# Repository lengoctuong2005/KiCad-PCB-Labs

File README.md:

# HCMUT - Thiết Kế Mạch In PCB với KiCad (Khóa Hè)

Tập hợp toàn bộ các bài thực hành và đồ án thiết kế PCB (KiCad) trong khóa học Thiết kế Mạch In / Vi Mạch.

## 📂 Danh mục bài tập (Labs & Project)

- **Common_Libraries/**: Thư viện linh kiện Footprint và Symbol tự tạo dùng chung.
- **Lab1/**: Thiết kế Mạch Nguồn Cơ Bản (Schematic, PCB Layout, Báo cáo kỹ thuật).
- **Lab2/**: Mạch Khuếch Đại / Cảm Biến & Sắp xếp linh kiện tiêu chuẩn.
- **Lab3/**: Mạch Giao Tiếp & Chuyển Đổi Nguồn (Schematic, Routing 2 lớp, BOM, Báo cáo & Kiểm tra DRC/ERC).
- **Lab4/**: Mạch Vi Điều Khiển / Ngoại Vi Mở Rộng.
- **Lab5/**: Thiết Kế Mạch RF / Cao Tần & Layout Nâng Cao.
- **Lab6/**: Tổng Hợp Thiết Kế Hoàn Chỉnh & Xuất File Gia Công (Gerber, Drill, BOM, CPL).
- **DoAn/**: Tài liệu và danh mục đề tài Đồ Án Cuối Khóa.

## 🛠️ Công cụ sử dụng
- **KiCad EDA v8 / v9**
- Schematic Editor (`.kicad_sch`)
- PCB Editor (`.kicad_pcb`)
- Footprint & Symbol Libraries (`.kicad_mod`, `.kicad_sym`)

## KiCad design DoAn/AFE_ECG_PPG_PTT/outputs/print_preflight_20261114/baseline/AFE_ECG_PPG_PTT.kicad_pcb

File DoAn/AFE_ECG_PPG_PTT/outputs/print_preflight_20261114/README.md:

# Gói kiểm trước đặt PCB trần và bộ tài liệu bench, cập nhật 18/11/2026

## Phạm vi bàn giao

PCB prototype 92 x 70 mm, hai lớp, dùng cho thử nghiệm bench với tín hiệu giả lập. Bản cập nhật ngày 18/11/2026 bổ sung đầy đủ thuộc tính `MPN` và `LCSC` đồng nhất trên toàn bộ 46 ký hiệu schematic và 46 footprint PCB, tạo `BOM_Orderable_LCSC.csv` đặt hàng LCSC, dựng bộ ảnh kiểm tra CAM từ dữ liệu Gerber và Excellon thực tế trong ZIP, và tạo bản đồ hàn lắp tương tác `Interactive_Soldering_Guide.html`. Không thay đổi `firmware/esp32_ptt_streamer/main.c` và `main/main.c`. Không chứng minh mạch hoạt động hoặc an toàn dùng trên người.

**File gửi CAM:** `GERBER_ONLY_92x70_NOT_CAM_APPROVED.zip`. Có đúng 11 file cấp gốc: 9 Gerber và 2 Excellon, không PDF/README/BOM/build. `.gbrjob` nằm ngoài ZIP.

## Kiểm đã làm ngày 18/11/2026

- KiCad 10.0.8 DRC với `--refill-zones --all-track-errors --schematic-parity --severity-all --exit-code-violations`: 0 violation, 0 unconnected, 0 schematic parity kể cả `footprint_symbol_field_mismatch`, `ignored_checks` rỗng.
- ERC đạt 0 Errors và 0 Warnings; giữ hai kiểm không áp dụng `global label only appears once` và `SPICE model issue` trong `erc.rpt`.
- Kiểm profile tạm `min_silk_clearance` 0,15 mm, `silk_over_copper` = error, `silk_overlap` = error, `silk_edge_clearance` = error đạt 0 lỗi trong `drc_fab_silk15.json`.
- Bảy kiểm regression `tests/check_*.py` đều PASS và 10/10 cổng `tools/bench_bringup_verify.py --preflight` đều PASS.
- 90 lỗ/slot khớp PCB trong 0,0011 mm: 38 via drill 0,3 mm; 48 lỗ/slot tool 1 mm gồm 3 slot `G85` tại `J1`; 4 lỗ M3 3,2 mm có mạ. NPTH file rỗng là chủ ý.
- Dựng kiểm tra CAM trực tiếp từ các tệp giải nén trong ZIP bằng Pillow/Excellon parser tại `CAM_top.png`, `CAM_bottom.png`, `CAM_mask.png`, `CAM_paste.png` và lưu thông số vào `gerbv_logs.json`: xác nhận 3 slot `G85` ở `J1`, 38/38 via phủ mask kín trên cả `F.Mask` và `B.Mask`, và 4 cửa sổ stencil phân đoạn `1,05 x 1,05 mm` đạt 65,2% diện tích trên EP của `U1`. Môi trường chạy không cài `gerbv`, nên cần đối chiếu thêm bằng preview CAM của xưởng trước khi thanh toán.
- `BOM.csv` xuất đủ 6 cột `Reference,Value,Footprint,MPN,LCSC,Quantity` cho 46 hàng; `BOM_Orderable_LCSC.csv` gồm 20 dòng linh kiện đặt hàng với `J2` số lượng 2 thanh.
- `Interactive_Soldering_Guide.html` tạo từ tọa độ thực trong `.kicad_pcb` cùng bảng MPN/LCSC và điểm kiểm tra `TP1..TP7`.
- `manifest.json` lưu mã băm SHA-256 của toàn bộ tệp nguồn, test và gói xuất hiện hành.

## Cách đặt và hàn lắp

Đọc `../HUONG_DAN_IN_HAN_VA_NGHIEM_THU.md`, `DAT_PCB_TRAN.md` và `FAB_PROFILE.md`. In `Assembly_1to1.pdf` tỷ lệ 100% đối chiếu module thực và mở `Interactive_Soldering_Guide.html` khi hàn lắp.

## Các cổng chưa đóng

1. Trước thanh toán: xác nhận preview CAM của xưởng nhận đúng 92 x 70 mm, 2 lớp, 3 slot `G85` của `J1`, 38 via tented và 4 lỗ M3 mạ; kiểm tồn kho thực tế của `U2` `C37593`, `C6/C7` `C82282`, `R16/R17` `C23162`, `R18` `C38070` và khớp cơ khí `J1` `SJ1-3533N`.
2. Trước lắp và cấp nguồn: kiểm tra pinout 7 chân và pull-up của module `MAX30102` thực mua ngoài, kiểm tra khớp chân ESP32 DevKitC V4 38 chân với `J2`.
3. Sau lắp: chạy `tools/esp32_bench_diag/esp32_bench_diag.ino` kiểm tra I2C và ngưỡng LOD `1400 mV` trên `GPIO32`/`GPIO33`, thực hiện đo 7 bước bench với máy giả lập và giữ nguyên khóa PAT live do `TIMESTAMP_UNCERTAIN`.

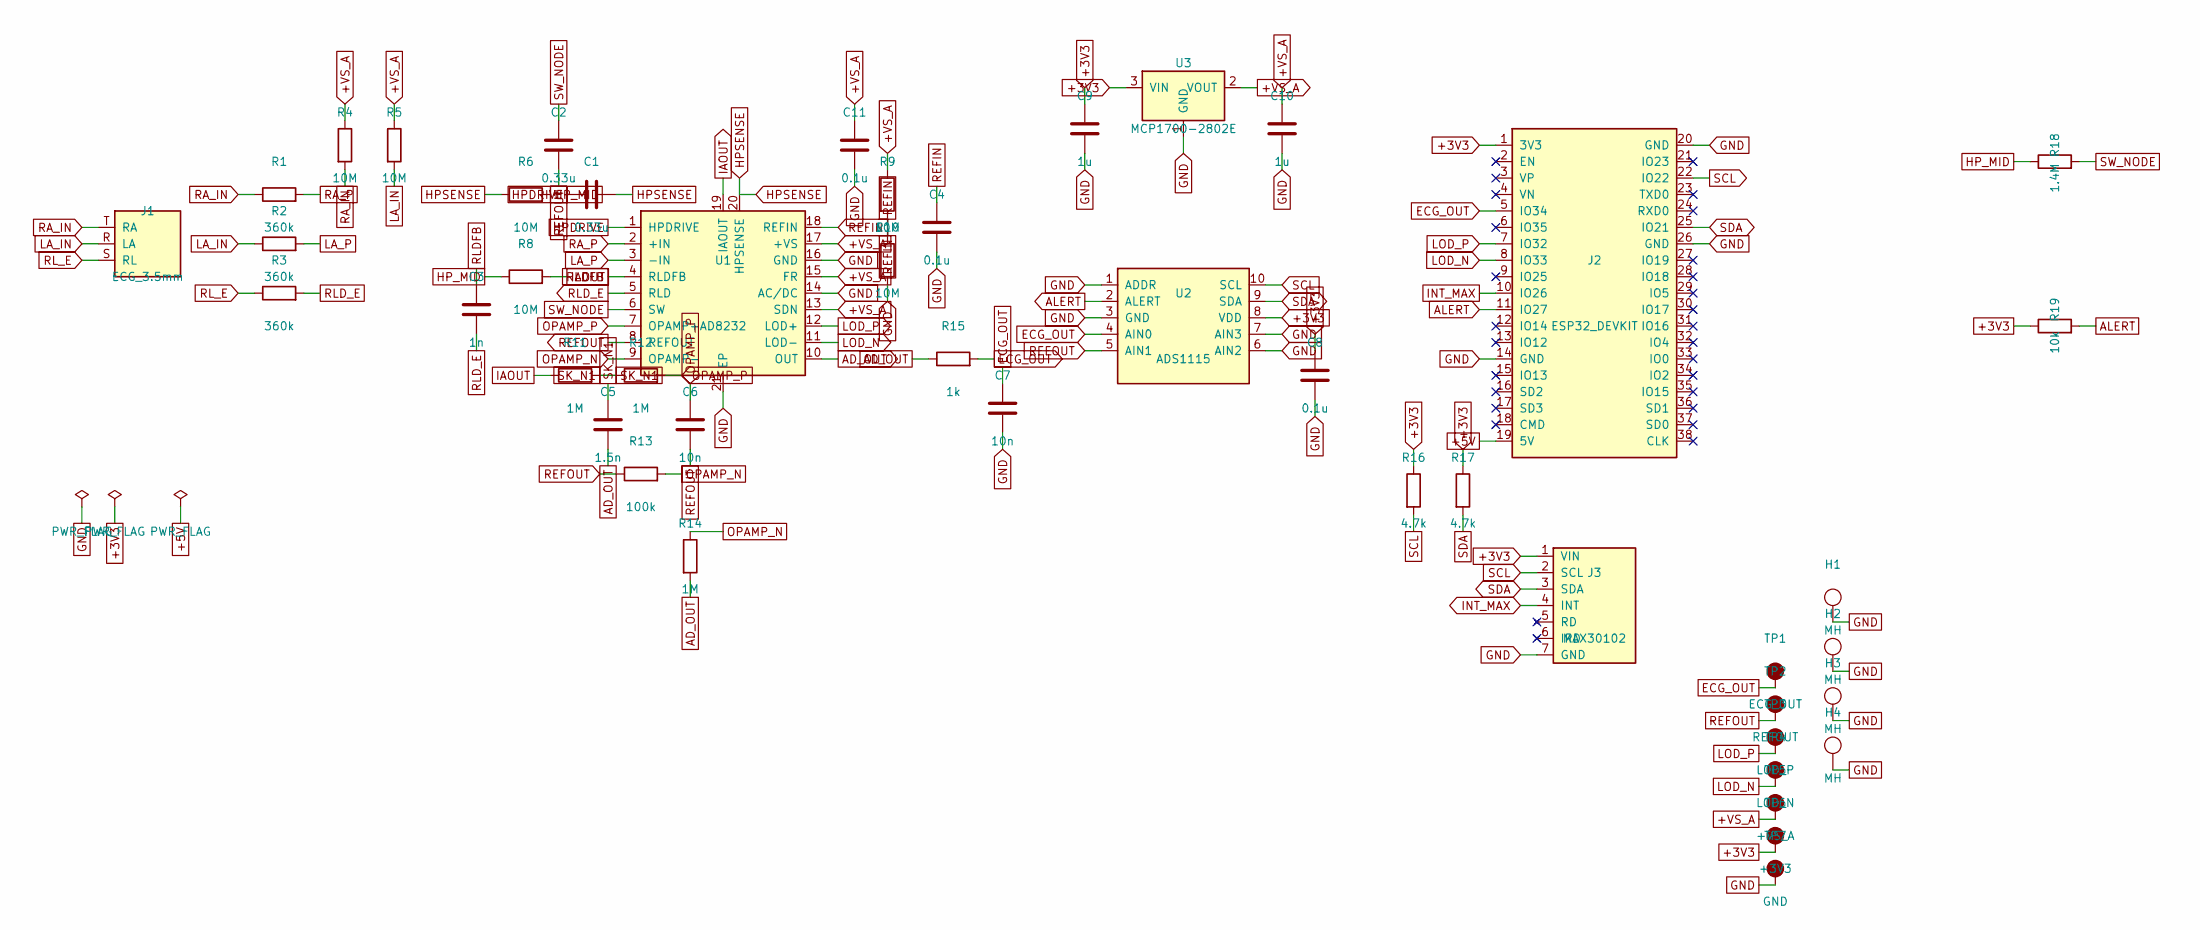
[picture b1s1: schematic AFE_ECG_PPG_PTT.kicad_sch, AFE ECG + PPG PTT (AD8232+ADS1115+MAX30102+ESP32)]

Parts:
C1, C2: 0.33u; C_0603_1608Metric
C3: 1n; C_0603_1608Metric
C4, C8, C11: 0.1u; C_0603_1608Metric
C5: 1.5n; C_0603_1608Metric
C6, C7: 10n; C_0603_1608Metric
C9, C10: 1u; C_0603_1608Metric
H1, H2, H3, H4: MH; MountingHole_3.2mm_M3_Pad
J1: ECG_3.5mm; Jack_3.5mm_CUI_SJ1-3533NG_Horizontal
J2: ESP32_DEVKIT; ESP32_DevKitC_V4_38P
J3: MAX30102; PinHeader_1x07_P2.54mm_Vertical
R1, R2, R3: 360k; R_0603_1608Metric
R4, R5, R6, R8, R9, R10: 10M; R_0603_1608Metric
R11, R12, R14: 1M; R_0603_1608Metric
R13: 100k; R_0603_1608Metric
R15: 1k; R_0603_1608Metric
R16, R17: 4.7k; R_0603_1608Metric
R18: 1.4M; R_0603_1608Metric
R19: 10k; R_0603_1608Metric
TP1: ECG_OUT; TestPoint_Pad_D1.5mm
TP2: REFOUT; TestPoint_Pad_D1.5mm
TP3: LOD_P; TestPoint_Pad_D1.5mm
TP4: LOD_N; TestPoint_Pad_D1.5mm
TP5: +VS_A; TestPoint_Pad_D1.5mm
TP6: +3V3; TestPoint_Pad_D1.5mm
TP7: GND; TestPoint_Pad_D1.5mm
U1: AD8232; LFCSP-20-1EP_4x4mm_P0.5mm_EP2.6x2.6mm
U2: ADS1115; TSSOP-10_3x3mm_P0.5mm
U3: MCP1700-2802E; SOT-23

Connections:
+3V3: C8.1, C9.1, J2.1 (3V3), J3.1 (VIN), R16.1, R17.1, R19.1, TP6.1, U2.8 (VDD), U3.3 (VIN)
+5V: J2.19 (5V)
+VS_A: C10.1, C11.1, R4.1, R5.1, R9.1, TP5.1, U1.13 (SDN), U1.15 (FR), U1.17 (+VS), U3.2 (VOUT)
AD_OUT: C5.2, R14.2, R15.1, U1.10 (OUT)
ALERT: J2.11 (IO27), R19.2, U2.2 (ALERT)
ECG_OUT: C7.1, J2.5 (IO34), R15.2, TP1.1, U2.4 (AIN0)
GND: C4.2, C7.2, C8.2, C9.2, C10.2, C11.2, H1.1, H2.1, H3.1, H4.1, J2.14 (GND), J2.20 (GND), J2.26 (GND), J3.7 (GND), R10.2, TP7.1, U1.14 (AC/DC), U1.16 (GND), U1.21 (EP), U2.1 (ADDR), U2.3 (GND), U2.6 (AIN2), U2.7 (AIN3), U3.1 (GND)
HPDRIVE: C1.1, U1.1 (HPDRIVE)
HPSENSE: C1.2, R6.1, U1.20 (HPSENSE)
HP_MID: R6.2, R8.1, R18.1
IAOUT: R8.2, R11.1, U1.19 (IAOUT)
INT_MAX: J2.10 (IO26), J3.4 (INT)
LA_IN: J1.R (LA), R2.1, R5.2
LA_P: R2.2, U1.3 (-IN)
LOD_N: J2.8 (IO33), TP4.1, U1.11 (LOD-)
LOD_P: J2.7 (IO32), TP3.1, U1.12 (LOD+)
OPAMP_N: R13.2, R14.1, U1.9 (OPAMP-)
OPAMP_P: C6.1, R12.2, U1.7 (OPAMP+)
RA_IN: J1.T (RA), R1.1, R4.2
RA_P: R1.2, U1.2 (+IN)
REFIN: C4.1, R9.2, R10.1, U1.18 (REFIN)
REFOUT: C2.2, C6.2, R13.1, TP2.1, U1.8 (REFOUT), U2.5 (AIN1)
RLDFB: C3.1, U1.4 (RLDFB)
RLD_E: C3.2, R3.2, U1.5 (RLD)
RL_E: J1.S (RL), R3.1
SCL: J2.22 (IO22), J3.2 (SCL), R16.2, U2.10 (SCL)
SDA: J2.25 (IO21), J3.3 (SDA), R17.2, U2.9 (SDA)
SK_N1: C5.1, R11.2, R12.1
SW_NODE: C2.1, R18.2, U1.6 (SW)

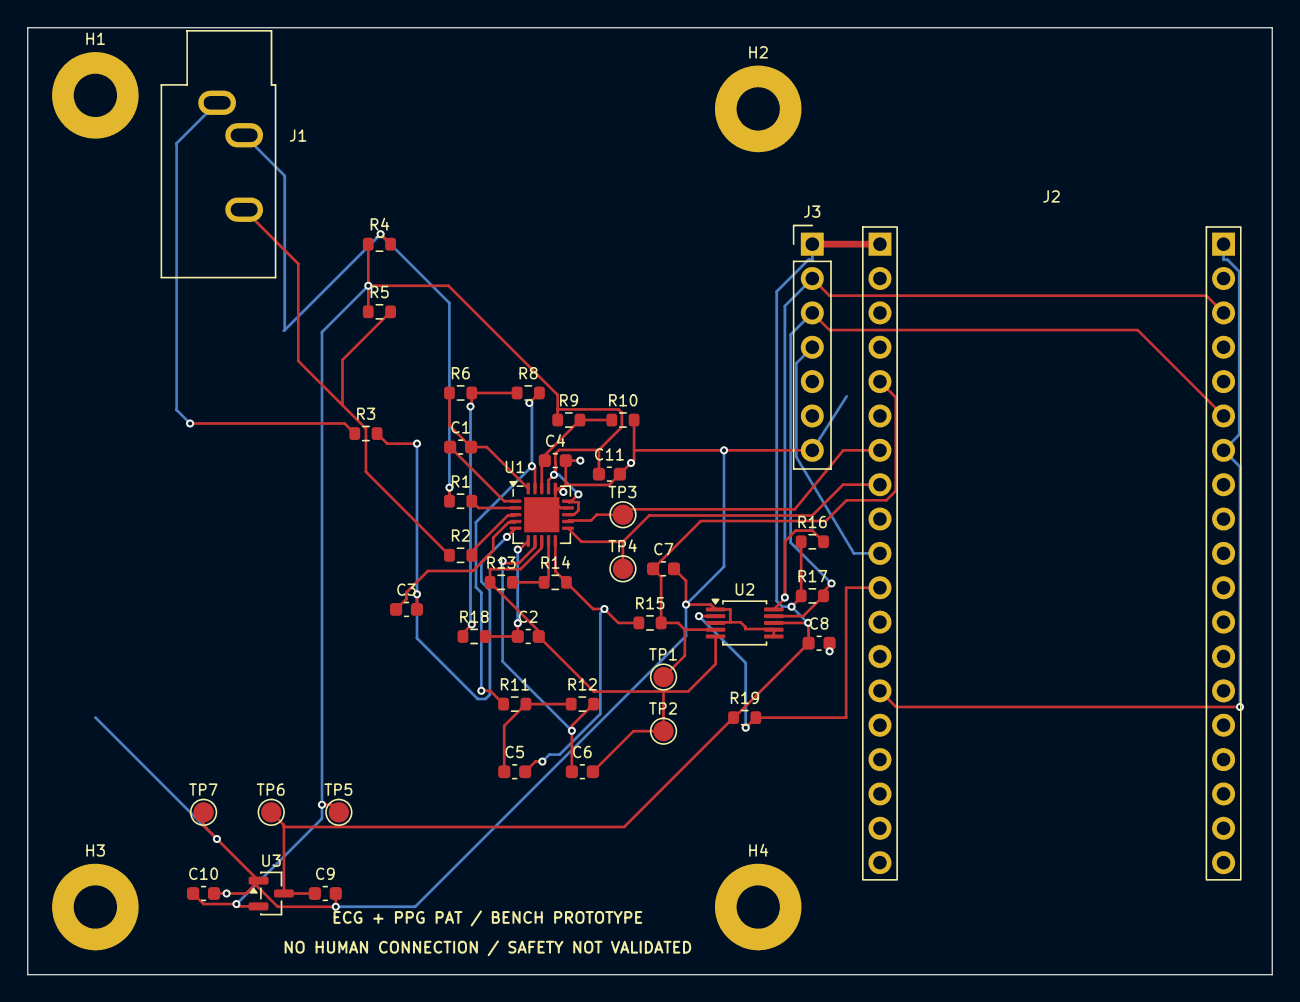
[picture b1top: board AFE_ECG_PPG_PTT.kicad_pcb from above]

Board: 2 copper layers, 92.0 x 70.0 mm, 46 parts (0 on the bottom side), 28 nets.

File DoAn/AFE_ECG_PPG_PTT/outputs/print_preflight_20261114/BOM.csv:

"Reference","Value","Footprint","MPN","LCSC","Quantity"
"C1","0.33u","Capacitor_SMD:C_0603_1608Metric","0603B334K250CT","C384782","1"
"C2","0.33u","Capacitor_SMD:C_0603_1608Metric","0603B334K250CT","C384782","1"
"C3","1n","Capacitor_SMD:C_0603_1608Metric","GCM1885C2A102JA16D","C437457","1"
"C4","0.1u","Capacitor_SMD:C_0603_1608Metric","MT18B104K500CT","C323570","1"
"C5","1.5n","Capacitor_SMD:C_0603_1608Metric","GRM1885C1H152JA01D","C162204","1"
"C6","10n","Capacitor_SMD:C_0603_1608Metric","0603CG103J500NT","C82282","1"
"C7","10n","Capacitor_SMD:C_0603_1608Metric","0603CG103J500NT","C82282","1"
"C8","0.1u","Capacitor_SMD:C_0603_1608Metric","MT18B104K500CT","C323570","1"
"C9","1u","Capacitor_SMD:C_0603_1608Metric","TCC0603X7R105K500CT","C5360793","1"
"C10","1u","Capacitor_SMD:C_0603_1608Metric","TCC0603X7R105K500CT","C5360793","1"
"C11","0.1u","Capacitor_SMD:C_0603_1608Metric","MT18B104K500CT","C323570","1"
"H1","MH","MountingHole:MountingHole_3.2mm_M3_Pad","PCB_INTEGRATED","DNP","1"
"H2","MH","MountingHole:MountingHole_3.2mm_M3_Pad","PCB_INTEGRATED","DNP","1"
"H3","MH","MountingHole:MountingHole_3.2mm_M3_Pad","PCB_INTEGRATED","DNP","1"
"H4","MH","MountingHole:MountingHole_3.2mm_M3_Pad","PCB_INTEGRATED","DNP","1"
"J1","ECG_3.5mm","Connector_Audio:Jack_3.5mm_CUI_SJ1-3533NG_Horizontal","SJ1-3533N","C4992360","1"
"J2","ESP32_DEVKIT","afe:ESP32_DevKitC_V4_38P","22850120ANG1SYA01","C429947","1"
"J3","MAX30102","Connector_PinHeader_2.54mm:PinHeader_1x07_P2.54mm_Vertical","2541WV-07P","C25503132","1"
"R1","360k","Resistor_SMD:R_0603_1608Metric","RCT03360KFLF","C177519","1"
"R2","360k","Resistor_SMD:R_0603_1608Metric","RCT03360KFLF","C177519","1"
"R3","360k","Resistor_SMD:R_0603_1608Metric","RCT03360KFLF","C177519","1"
"R4","10M","Resistor_SMD:R_0603_1608Metric","AC0603FR-0710ML","C227547","1"
"R5","10M","Resistor_SMD:R_0603_1608Metric","AC0603FR-0710ML","C227547","1"
"R6","10M","Resistor_SMD:R_0603_1608Metric","AC0603FR-0710ML","C227547","1"
"R8","10M","Resistor_SMD:R_0603_1608Metric","AC0603FR-0710ML","C227547","1"
"R9","10M","Resistor_SMD:R_0603_1608Metric","AC0603FR-0710ML","C227547","1"
"R10","10M","Resistor_SMD:R_0603_1608Metric","AC0603FR-0710ML","C227547","1"
"R11","1M","Resistor_SMD:R_0603_1608Metric","CRCW06031M00FKEA","C844922","1"
"R12","1M","Resistor_SMD:R_0603_1608Metric","CRCW06031M00FKEA","C844922","1"
"R13","100k","Resistor_SMD:R_0603_1608Metric","CRCW0603100KFKTA","C844120","1"
"R14","1M","Resistor_SMD:R_0603_1608Metric","CRCW06031M00FKEA","C844922","1"
"R15","1k","Resistor_SMD:R_0603_1608Metric","ERJPA3F1001V","C441922","1"
"R16","4.7k","Resistor_SMD:R_0603_1608Metric","0603WAF4701T5E","C23162","1"
"R17","4.7k","Resistor_SMD:R_0603_1608Metric","0603WAF4701T5E","C23162","1"
"R18","1.4M","Resistor_SMD:R_0603_1608Metric","0603WAF1404T5E","C38070","1"
"R19","10k","Resistor_SMD:R_0603_1608Metric","CRGCQ0603F10K","C4210728","1"
"TP1","ECG_OUT","TestPoint:TestPoint_Pad_D1.5mm","PCB_INTEGRATED","DNP","1"
"TP2","REFOUT","TestPoint:TestPoint_Pad_D1.5mm","PCB_INTEGRATED","DNP","1"
"TP3","LOD_P","TestPoint:TestPoint_Pad_D1.5mm","PCB_INTEGRATED","DNP","1"
"TP4","LOD_N","TestPoint:TestPoint_Pad_D1.5mm","PCB_INTEGRATED","DNP","1"
"TP5","+VS_A","TestPoint:TestPoint_Pad_D1.5mm","PCB_INTEGRATED","DNP","1"
"TP6","+3V3","TestPoint:TestPoint_Pad_D1.5mm","PCB_INTEGRATED","DNP","1"
"TP7","GND","TestPoint:TestPoint_Pad_D1.5mm","PCB_INTEGRATED","DNP","1"
"U1","AD8232","Package_CSP:LFCSP-20-1EP_4x4mm_P0.5mm_EP2.6x2.6mm","AD8232ACPZ-R7","C43216","1"
"U2","ADS1115","Package_SO:TSSOP-10_3x3mm_P0.5mm","ADS1115IDGSR","C37593","1"
"U3","MCP1700-2802E","Package_TO_SOT_SMD:SOT-23","MCP1700T-2802E/TT","C625349","1"

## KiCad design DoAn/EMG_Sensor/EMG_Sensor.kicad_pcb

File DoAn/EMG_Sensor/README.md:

# Đồ Án: Thiết Bị Đo Tín Hiệu Điện Cơ Bề Mặt (sEMG Analog Front-End)

## 1. Giới thiệu tổng quan
Dự án thiết kế hoàn chỉnh từ đầu (scratch) mạch thu nhận và xử lý tín hiệu điện cơ bề mặt (**Surface Electromyography - sEMG**) dùng trong các ứng dụng y sinh, điều khiển cánh tay robot sinh học (prosthetics), nhận diện cử chỉ cơ bắp và theo dõi vận động thể thao.

Thiết kế đạt **0 lỗi ERC** (Schematic Electrical Rules Check) và **0 lỗi DRC** (Design Rules Check) trên KiCad 8/10, sẵn sàng 100% cho gia công sản xuất công nghiệp (JLCPCB, PCBWay).

---

## 2. Thông số kỹ thuật chính (Specifications)

| Thông số | Giá trị | Ghi chú |
| :--- | :--- | :--- |
| **Điện áp nguồn ($V_{CC}$)** | 3.3V – 5.0V DC | Tương thích trực tiếp ESP32, STM32, Arduino |
| **Dòng tiêu thụ** | < 3.5 mA | Tiết kiệm năng lượng cho thiết bị đeo (wearable) |
| **Băng thông tần số EMG** | 20 Hz – 450 Hz | Chuẩn y tế loại bỏ nhiễu chuyển động và khử răng cưa |
| **Độ khuếch đại tổng (Total Gain)** | ~1010× (60.1 dB) | Tầng 1: $101\times$, Tầng 2: $10.1\times$ |
| **CMRR (Common Mode Rejection)** | > 100 dB @ 50/60 Hz | Nhờ khuếch đại vi sai AD623 & điện cực tham chiếu |
| **Tín hiệu đầu ra 1 (`RAW_EMG`)** | Centered @ $V_{\text{REF}}$ ($V_{CC}/2$) | Phân tích phổ tần số, mỏi cơ, FFT |
| **Tín hiệu đầu ra 2 (`ENV_EMG`)** | 0V – $V_{CC}$ DC Envelope | Đọc trực tiếp qua ADC vi điều khiển để trigger hành động |
| **Chỉ thị trực quan** | 2 LED SMD 0805 | LED xanh (Nguồn), LED đỏ (Cường độ co cơ) |
| **Kích thước bo mạch** | 50.0 mm × 30.0 mm | 2 lớp FR4 1.6mm, 4 lỗ bắt ốc M2 cách ly |

---

## 3. Kiến trúc mạch & Nguyên lý hoạt động

Mạch được thiết kế theo cấu trúc khối chuẩn công nghiệp:

```
[Điện cực IN+/IN-/REF]
         │
         ▼
[1. Khối lọc R-C EMI & Phân cực 10MΩ]
         │
         ▼
[2. Khuếch đại đo lường AD623ARZ (G1 = 101)]
         │
         ▼
[3. Mạch lọc thông cao chủ động HPF (fc ≈ 20 Hz)]
         │
         ▼
[4. Mạch lọc thông thấp Sallen-Key bậc 2 + Gain (fc ≈ 450 Hz, G2 = 10)]
         │
         ├─────────────────────────────────────────► [Đầu ra RAW_EMG (J3.3)]
         │
         ▼
[5. Mạch chỉnh lưu toàn sóng chính xác (Ideal Diode Detector)]
         │
         ▼
[6. Mạch lọc bao hình tích phân (Leaky Integrator, fc ≈ 5 Hz)]
         │
         ├─────────────────────────────────────────► [Đầu ra ENV_EMG (J3.4)]
         │
         ▼
[7. Đèn LED hiển thị lực co cơ (Red ACT LED)]
```

### Chi tiết các linh kiện cốt lõi:
1. **AD623ARZ (U1)**: IC khuếch đại đo lường vi sai chuyên dụng (Instrumentation Amplifier) đường nguồn đơn (Single-Supply Rail-to-Rail). Điện trở định độ lợi $R_8 = 1.0\text{ k}\Omega \Rightarrow G_1 = 1 + \frac{100\text{ k}\Omega}{1\text{ k}\Omega} = 101$.
2. **MCP6004-E/SL (U2)**: IC tích hợp 4 khuếch đại thuật toán Rail-to-Rail I/O độ ồn thấp:
   - **U2A**: Mạch đệm điện áp ảo ($V_{\text{REF}} = V_{CC}/2$) cung cấp đường mass ảo trở kháng cực thấp cho toàn hệ thống.
   - **U2B**: Mạch lọc thông thấp Sallen-Key bậc 2 tần số cắt 450 Hz kết hợp khuếch đại $10.1\times$ ($R_{12}=10\text{k}\Omega, R_{13}=91\text{k}\Omega$).
   - **U2C**: Mạch chỉnh lưu toàn sóng chính xác không suy hao diode kết hợp cặp diode xung $1N4148W$.
   - **U2D**: Mạch tích phân lọc bao hình cơ vân tần số cắt 4.8 Hz ($R_{18}=100\text{k}\Omega, C_{12}=330\text{nF}$).

---

## 4. Bố trí giắc cắm & Kết nối (Pinout)

### Giắc tín hiệu điện cực (J2 - 3 Pin 2.54mm):
- **Pin 1 (IN+)**: Điện cực đo dương (dán trên bắp cơ cần đo).
- **Pin 2 (IN-)**: Điện cực đo âm (dán dọc theo thớ cơ, cách điện cực dương 15-20mm).
- **Pin 3 (REF)**: Điện cực tham chiếu cơ thể (Body Reference / Ground, dán tại vùng xương trung tính như khuỷu tay hoặc cổ tay).

### Giắc cấp nguồn & đầu ra (J3 - 4 Pin 2.54mm):
- **Pin 1 (VCC)**: Điện áp nguồn 3.3V – 5.0V DC.
- **Pin 2 (GND)**: Mass nguồn hệ thống 0V.
- **Pin 3 (RAW)**: Tín hiệu thô đã lọc dải (20 Hz - 450 Hz), biên độ $\pm 1.5\text{V}$ quanh $V_{REF}$.
- **Pin 4 (ENV)**: Tín hiệu bao hình lực cơ bắp (0V - 3.3V/5V DC), tỷ lệ thuận với lực gồng cơ.

### Giắc nguồn phụ (J1 - 2 Pin 2.54mm):
- **Pin 1**: VCC | **Pin 2**: GND.

---

## 5. Kết quả kiểm tra thiết kế (Verification & Compliance)

| Công cụ kiểm tra | Lệnh thực thi | Kết quả | Đánh giá |
| :--- | :--- | :--- | :--- |
| **KiCad ERC** | `kicad-cli sch erc EMG_Sensor.kicad_sch` | **0 violations, 0 errors** | Đạt chuẩn điện Schematic |
| **KiCad DRC** | `kicad-cli pcb drc EMG_Sensor.kicad_pcb` | **0 violations, 0 unconnected** | Đạt chuẩn thiết kế PCB |
| **Netlist & Clearance** | Netclass default (0.20mm min) | **100% pass (≥ 0.25mm)** | Cách điện an toàn |
| **Mặt phẳng mass (GND)** | F.Cu & B.Cu thermal relief | **Đồng bộ hóa qua via stitching** | Giảm thiểu tối đa can nhiễu 50Hz |

---

## 6. Hồ sơ xuất xưởng (Outputs)

Tất cả các tệp phục vụ chế tạo bo mạch được xuất đầy đủ trong thư mục `outputs/`:
- **Gerber Files**: `EMG_Sensor-F_Cu.gbr`, `EMG_Sensor-B_Cu.gbr`, `EMG_Sensor-F_Mask.gbr`, `EMG_Sensor-B_Mask.gbr`, `EMG_Sensor-F_Silkscreen.gbr`, `EMG_Sensor-B_Silkscreen.gbr`, `EMG_Sensor-Edge_Cuts.gbr`.
- **Drill Files**: `EMG_Sensor.drl`, `EMG_Sensor-NPTH.drl`.
- **Danh mục linh kiện (BOM)**: `outputs/BOM_EMG_Sensor.csv` (41 linh kiện chi tiết).
- **Báo cáo kỹ thuật**: `outputs/drc_report.json`, `outputs/erc_report.rpt`.
- **Bản vẽ trực quan 2D**: `outputs/EMG_Sensor_Top.svg`, `outputs/EMG_Sensor_Bottom.svg`.

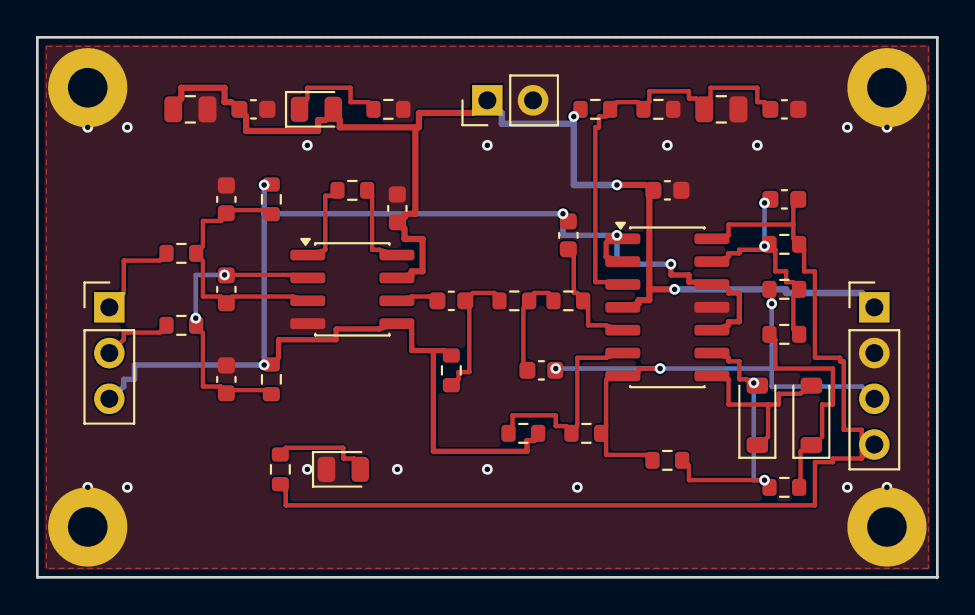
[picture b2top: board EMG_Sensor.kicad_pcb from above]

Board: 2 copper layers, 50.0 x 30.0 mm, 45 parts (0 on the bottom side), 23 nets.

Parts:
C1, C3: 10uF; C_0805_2012Metric
C2, C4, C8, C13: 100nF; C_0603_1608Metric
C5: 100pF; C_0603_1608Metric
C6, C7: 47pF; C_0603_1608Metric
C9: 1uF; C_0603_1608Metric
C10: 15nF; C_0603_1608Metric
C11: 6.8nF; C_0603_1608Metric
C12: 330nF; C_0603_1608Metric
D1: Green_PWR; LED_0805_2012Metric
D2, D3: 1N4148W; D_SOD-123
D4: Red_ACT; LED_0805_2012Metric
H1, H2, H3, H4: M2; MountingHole_2.2mm_M2_Pad
J1: Power_In; PinHeader_1x02_P2.54mm_Vertical
J2: Electrodes_In; PinHeader_1x03_P2.54mm_Vertical
J3: EMG_Out; PinHeader_1x04_P2.54mm_Vertical
R1, R4, R5, R8, R19: 1k; R_0603_1608Metric
R2, R3, R18: 100k; R_0603_1608Metric
R6, R7: 10M; R_0603_1608Metric
R9: 8.2k; R_0603_1608Metric
R10, R11: 22k; R_0603_1608Metric
R12, R14, R15, R17: 10k; R_0603_1608Metric
R13: 91k; R_0603_1608Metric
R16: 20k; R_0603_1608Metric
U1: AD623ARZ; SOIC-8_3.9x4.9mm_P1.27mm
U2: MCP6004-E/SL; SOIC-14_3.9x8.7mm_P1.27mm

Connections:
ENV_EMG: C12.2, J3.4, R18.2, R19.1, U2.14
ENV_IN: C12.1, R16.2, R17.2, R18.1, U2.13
GND: C1.2, C2.2, C3.2, C4.2, C6.2, C7.2, C8.2, C13.2, D4.1, H1.1, H2.1, H3.1, H4.1, J1.2, J3.2, R1.2, R3.2, U1.4, U2.11
HPF_OUT: C9.2, R9.1, R10.1
IN_MINUS_FILT: C5.2, C7.1, R5.2, R7.1, U1.2
IN_MINUS_RAW: J2.2, R5.1
IN_PLUS_FILT: C5.1, C6.1, R4.2, R6.1, U1.3
IN_PLUS_RAW: J2.1, R4.1
LPF_FB: R12.1, R13.1, U2.6
LPF_IN: C11.1, R11.2, U2.5
LPF_NODE: C10.1, R10.2, R11.1
NET_D1_R1: D1.1, R1.1
NET_D4_R19: D4.2, R19.2
RAW_EMG: C10.2, J3.3, R13.2, R14.1, R17.1, U2.7
RECT_HALF: D3.1, R15.2, R16.1
RECT_IN: D2.2, R14.2, R15.1, U2.9
RECT_OUT: D2.1, D3.2, U2.8
RG1: R8.1, U1.1
RG2: R8.2, U1.8
VCC: C1.1, C2.1, C8.1, C13.1, D1.2, J1.1, J3.1, R2.1, U1.7, U2.4
VMID: C3.1, C4.1, R2.2, R3.1, U2.3
VOUT_IA: C9.1, U1.6
VREF: C11.2, J2.3, R6.2, R7.2, R9.2, R12.2, U1.5, U2.1, U2.2, U2.10, U2.12

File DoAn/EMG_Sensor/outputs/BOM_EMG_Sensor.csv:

"Refs","Value","Footprint","Qty","DNP"
"C1","10uF","Capacitor_SMD:C_0805_2012Metric","1",""
"C2","100nF","Capacitor_SMD:C_0603_1608Metric","1",""
"C3","10uF","Capacitor_SMD:C_0805_2012Metric","1",""
"C4","100nF","Capacitor_SMD:C_0603_1608Metric","1",""
"C5","100pF","Capacitor_SMD:C_0603_1608Metric","1",""
"C6","47pF","Capacitor_SMD:C_0603_1608Metric","1",""
"C7","47pF","Capacitor_SMD:C_0603_1608Metric","1",""
"C8","100nF","Capacitor_SMD:C_0603_1608Metric","1",""
"C9","1uF","Capacitor_SMD:C_0603_1608Metric","1",""
"C10","15nF","Capacitor_SMD:C_0603_1608Metric","1",""
"C11","6.8nF","Capacitor_SMD:C_0603_1608Metric","1",""
"C12","330nF","Capacitor_SMD:C_0603_1608Metric","1",""
"C13","100nF","Capacitor_SMD:C_0603_1608Metric","1",""
"D1","Green_PWR","LED_SMD:LED_0805_2012Metric","1",""
"D2","1N4148W","Diode_SMD:D_SOD-123","1",""
"D3","1N4148W","Diode_SMD:D_SOD-123","1",""
"D4","Red_ACT","LED_SMD:LED_0805_2012Metric","1",""
"J1","Power_In","Connector_PinHeader_2.54mm:PinHeader_1x02_P2.54mm_Vertical","1",""
"J2","Electrodes_In","Connector_PinHeader_2.54mm:PinHeader_1x03_P2.54mm_Vertical","1",""
"J3","EMG_Out","Connector_PinHeader_2.54mm:PinHeader_1x04_P2.54mm_Vertical","1",""
"R1","1k","Resistor_SMD:R_0603_1608Metric","1",""
"R2","100k","Resistor_SMD:R_0603_1608Metric","1",""
"R3","100k","Resistor_SMD:R_0603_1608Metric","1",""
"R4","1k","Resistor_SMD:R_0603_1608Metric","1",""
"R5","1k","Resistor_SMD:R_0603_1608Metric","1",""
"R6","10M","Resistor_SMD:R_0603_1608Metric","1",""
"R7","10M","Resistor_SMD:R_0603_1608Metric","1",""
"R8","1k","Resistor_SMD:R_0603_1608Metric","1",""
"R9","8.2k","Resistor_SMD:R_0603_1608Metric","1",""
"R10","22k","Resistor_SMD:R_0603_1608Metric","1",""
"R11","22k","Resistor_SMD:R_0603_1608Metric","1",""
"R12","10k","Resistor_SMD:R_0603_1608Metric","1",""
"R13","91k","Resistor_SMD:R_0603_1608Metric","1",""
"R14","10k","Resistor_SMD:R_0603_1608Metric","1",""
"R15","10k","Resistor_SMD:R_0603_1608Metric","1",""
"R16","20k","Resistor_SMD:R_0603_1608Metric","1",""
"R17","10k","Resistor_SMD:R_0603_1608Metric","1",""
"R18","100k","Resistor_SMD:R_0603_1608Metric","1",""
"R19","1k","Resistor_SMD:R_0603_1608Metric","1",""
"U1","AD623ARZ","Package_SO:SOIC-8_3.9x4.9mm_P1.27mm","1",""
"U2","MCP6004-E/SL","Package_SO:SOIC-14_3.9x8.7mm_P1.27mm","1",""

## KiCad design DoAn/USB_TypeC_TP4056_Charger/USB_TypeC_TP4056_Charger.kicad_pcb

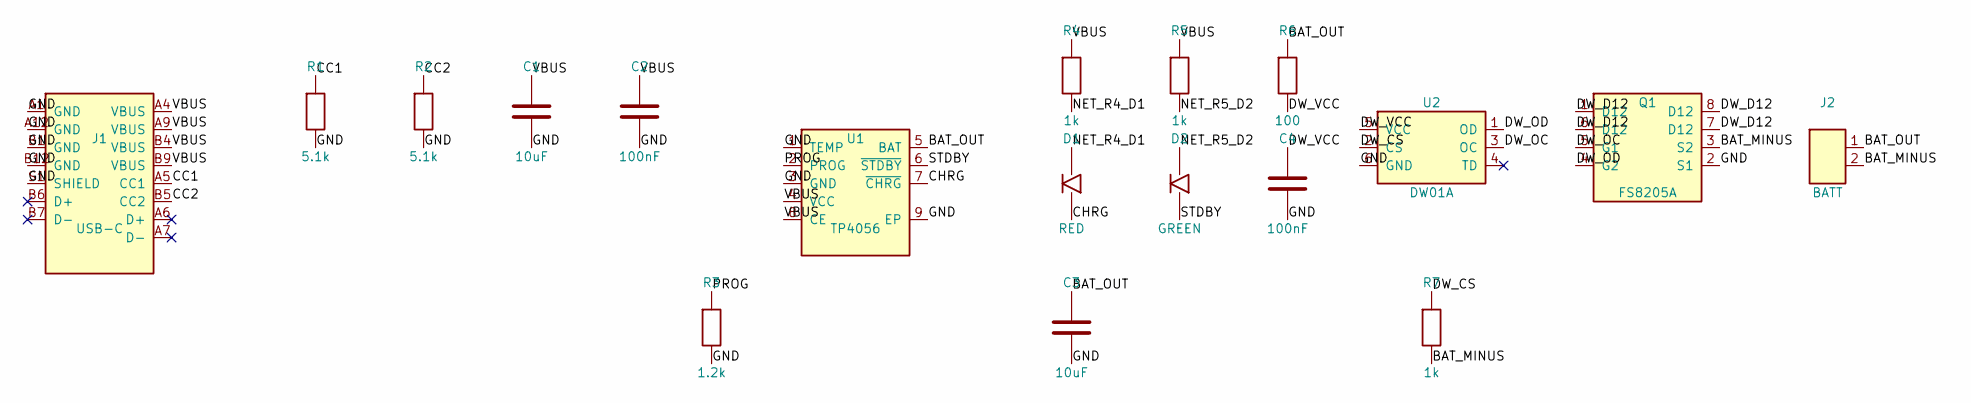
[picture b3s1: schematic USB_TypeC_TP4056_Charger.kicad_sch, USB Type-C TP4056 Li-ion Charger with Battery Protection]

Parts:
C1, C3: 10uF; C_0805_2012Metric
C2, C4: 100nF; C_0805_2012Metric
D1: RED; LED_0805_2012Metric
D2: GREEN; LED_0805_2012Metric
J1: USB-C; USB_C_Receptacle_HRO_TYPE-C-31-M-12
J2: BATT; JST_PH_B2B-PH-SM4-TB
Q1: FS8205A; TSSOP-8_4.4x3mm_P0.65mm
R1, R2: 5.1k; R_0805_2012Metric
R3: 1.2k; R_0805_2012Metric
R4, R5, R7: 1k; R_0805_2012Metric
R6: 100; R_0805_2012Metric
U1: TP4056; SOIC-8-1EP_3.9x4.9mm_P1.27mm_EP2.29x3.0mm
U2: DW01A; SOT-23-6

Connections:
BAT_MINUS: J2.2, Q1.3 (S2), R7.2
BAT_OUT: C3.1, J2.1, R6.1, U1.5 (BAT)
CC1: J1.A5 (CC1), R1.1
CC2: J1.B5 (CC2), R2.1
CHRG: D1.1 (K), U1.7 (~CHRG)
DW_CS: R7.1, U2.2 (CS)
DW_D12: Q1.1 (D12), Q1.6 (D12), Q1.7 (D12), Q1.8 (D12)
DW_OC: Q1.5 (G1), U2.3 (OC)
DW_OD: Q1.4 (G2), U2.1 (OD)
DW_VCC: C4.1, R6.2, U2.5 (VCC)
GND: C1.2, C2.2, C3.2, C4.2, J1.A1 (GND), J1.A12 (GND), J1.B1 (GND), J1.B12 (GND), J1.S1 (SHIELD), Q1.2 (S1), R1.2, R2.2, R3.2, U1.1 (TEMP), U1.3 (GND), U1.9 (EP), U2.6 (GND)
NET_R4_D1: D1.2 (A), R4.2
NET_R5_D2: D2.2 (A), R5.2
PROG: R3.1, U1.2 (PROG)
STDBY: D2.1 (K), U1.6 (~STDBY)
VBUS: C1.1, C2.1, J1.A4 (VBUS), J1.A9 (VBUS), J1.B4 (VBUS), J1.B9 (VBUS), R4.1, R5.1, U1.4 (VCC), U1.8 (CE)

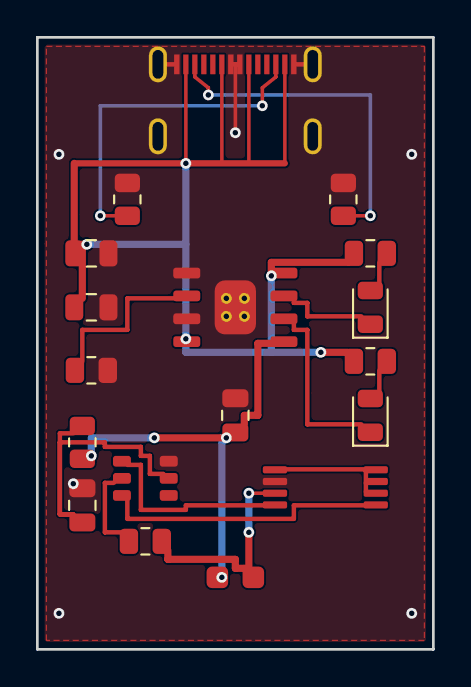
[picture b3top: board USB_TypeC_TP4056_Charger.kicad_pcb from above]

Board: 2 copper layers, 22.0 x 34.0 mm, 18 parts (0 on the bottom side), 16 nets.

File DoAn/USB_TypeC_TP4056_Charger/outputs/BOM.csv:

"Refs","Value","Footprint","Qty","DNP","LCSC","Description"
"C1","10uF","Capacitor_SMD:C_0805_2012Metric","1","","C15850","Samsung CL21A106KAYNNNE, 10uF 25V X5R 0805"
"C2","100nF","Capacitor_SMD:C_0805_2012Metric","1","","C49678","YAGEO CC0805KRX7R9BB104, 100nF 50V X7R 0805"
"C3","10uF","Capacitor_SMD:C_0805_2012Metric","1","","C15850","Samsung CL21A106KAYNNNE, 10uF 25V X5R 0805"
"C4","100nF","Capacitor_SMD:C_0805_2012Metric","1","","C49678","YAGEO CC0805KRX7R9BB104, 100nF 50V X7R 0805"
"D1","RED","LED_SMD:LED_0805_2012Metric","1","","C2295","KT-0805R red LED 0805"
"D2","GREEN","LED_SMD:LED_0805_2012Metric","1","","C2297","KT-0805G green LED 0805"
"J1","USB_C","charger:USB_C_Receptacle_HRO_TYPE-C-31-M-12","1","","C165948","HRO TYPE-C-31-M-12 USB Type-C receptacle"
"J2","BATT","charger:JST_PH_B2B-PH-SM4-TB","1","","C160352","JST B2B-PH-SM4-TB(LF)(SN), 2-pin PH 2.0mm SMD vertical"
"Q1","FS8205A","charger:TSSOP-8_4.4x3mm_P0.65mm","1","","C16052","Fortune FS8205A dual N-MOSFET TSSOP-8"
"R1","5.1k","Resistor_SMD:R_0805_2012Metric","1","","C27834","UNI-ROYAL 0805W8F5101T5E, 5.1k 1% 0805"
"R2","5.1k","Resistor_SMD:R_0805_2012Metric","1","","C27834","UNI-ROYAL 0805W8F5101T5E, 5.1k 1% 0805"
"R3","1.2k","Resistor_SMD:R_0805_2012Metric","1","","C17379","UNI-ROYAL 0805W8F1201T5E, 1.2k 1% 0805"
"R4","1k","Resistor_SMD:R_0805_2012Metric","1","","C17513","UNI-ROYAL 0805W8F1001T5E, 1k 1% 0805"
"R5","1k","Resistor_SMD:R_0805_2012Metric","1","","C17513","UNI-ROYAL 0805W8F1001T5E, 1k 1% 0805"
"R6","100","Resistor_SMD:R_0805_2012Metric","1","","C17408","UNI-ROYAL 0805W8F1000T5E, 100R 1% 0805"
"R7","1k","Resistor_SMD:R_0805_2012Metric","1","","C17513","UNI-ROYAL 0805W8F1001T5E, 1k 1% 0805"
"U1","TP4056","charger:SOIC-8-1EP_3.9x4.9mm_P1.27mm_EP2.29x3.0mm","1","","C16581","TP4056-42-ESOP8 lithium charger with exposed pad"
"U2","DW01A","charger:SOT-23-6","1","","C61503","Fortune DW01A-G single-cell protection IC SOT-23-6"

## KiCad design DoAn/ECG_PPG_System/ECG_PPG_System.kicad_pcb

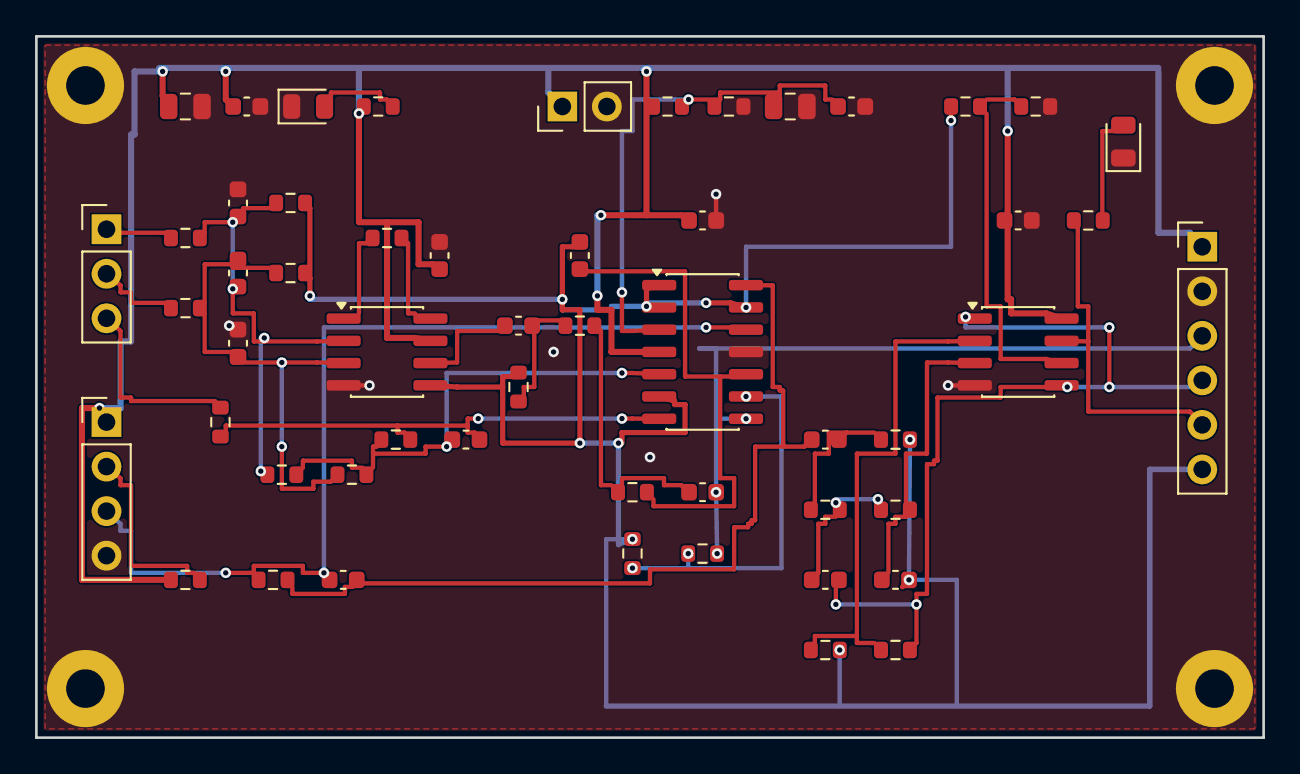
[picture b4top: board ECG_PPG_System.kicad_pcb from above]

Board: 2 copper layers, 70.0 x 40.0 mm, 58 parts (0 on the bottom side), 31 nets.

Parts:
C1, C3: 10uF; C_0805_2012Metric
C2, C4, C8, C11, C13, C18: 100nF; C_0603_1608Metric
C5: 100pF; C_0603_1608Metric
C6, C7: 47pF; C_0603_1608Metric
C9: 1nF; C_0603_1608Metric
C10, C15, C16: 1uF; C_0603_1608Metric
C12: 47nF; C_0603_1608Metric
C14: 22pF; C_0603_1608Metric
C17: 470nF; C_0603_1608Metric
D1: Green_PWR; LED_0805_2012Metric
D2: Red_PULSE; LED_0805_2012Metric
H1, H2, H3, H4: M2; MountingHole_2.2mm_M2_Pad
J1: Power_In; PinHeader_1x02_P2.54mm_Vertical
J2: ECG_Leads; PinHeader_1x03_P2.54mm_Vertical
J3: PPG_Sensor; PinHeader_1x04_P2.54mm_Vertical
J4: System_Out; PinHeader_1x06_P2.54mm_Vertical
R1, R2, R9, R10, R25: 100k; R_0603_1608Metric
R3, R4, R5, R8, R23, R27: 1k; R_0603_1608Metric
R6, R7: 10M; R_0603_1608Metric
R11, R18: 1M; R_0603_1608Metric
R12: 390k; R_0603_1608Metric
R13, R20: 330k; R_0603_1608Metric
R14, R15: 39k; R_0603_1608Metric
R16, R26: 10k; R_0603_1608Metric
R17: 91k; R_0603_1608Metric
R19: 220R; R_0603_1608Metric
R21, R22: 15k; R_0603_1608Metric
R24: 47k; R_0603_1608Metric
U1: AD623ARZ; SOIC-8_3.9x4.9mm_P1.27mm
U2: MCP6004-E/SL; SOIC-14_3.9x8.7mm_P1.27mm
U3: MCP6002-E/SN; SOIC-8_3.9x4.9mm_P1.27mm

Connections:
DRL_CM: C9.1, R9.2, R10.2, R11.1, U2.5
DRL_OUT: C9.2, R11.2, R12.1, U2.7
ECG_FB: R16.1, R17.1, U2.9
ECG_HPF_OUT: C10.2, R13.1, R14.1
ECG_IA_OUT: C10.1, U1.6
ECG_LPF_IN: C12.1, R15.2, U2.10
ECG_LPF_NODE: C11.1, R14.2, R15.1
ECG_OUT: C11.2, J4.3, R17.2, U2.8
GND: C1.2, C2.2, C3.2, C4.2, C6.2, C7.2, C8.2, C13.2, C18.2, D1.1, D2.1, H1.1, H2.1, H3.1, H4.1, J1.2, J3.4, J4.2, R2.2, R26.2, U1.4, U2.11, U3.4
LA_FILT: C5.2, C7.1, R5.2, R7.1, R10.1, U1.3
LA_RAW: J2.2, R5.1
LED_DRV: J3.2, R19.2
NET_D1_R3: D1.2, R3.2
NET_D2_R27: D2.2, R27.2
PD_ANODE: C14.1, J3.3, R18.1, U2.12
PPG_FB: R23.1, R24.1, U3.2
PPG_HPF_OUT: C15.2, R20.1, R21.1
PPG_LPF_IN: C17.1, R22.2, U3.3
PPG_LPF_NODE: C16.1, R21.2, R22.1
PPG_OUT: C16.2, J4.4, R24.2, U3.1, U3.5
PPG_TIA_OUT: C14.2, C15.1, R18.2, U2.14
PULSE_TRIG: J4.5, R27.1, U3.7
RA_FILT: C5.1, C6.1, R4.2, R6.1, R9.1, U1.2
RA_RAW: J2.1, R4.1
RG1: R8.1, U1.1
RG2: R8.2, U1.8
RL_DRL: J2.3, R12.2
VCC: C1.1, C2.1, C8.1, C13.1, C18.1, J1.1, J3.1, J4.1, R1.1, R3.1, R19.1, U1.7, U2.4, U3.8
VMID: C3.1, C4.1, R1.2, R2.1, U2.3
VREF: C12.2, C17.2, J4.6, R6.2, R7.2, R13.2, R16.2, R20.2, R23.2, R25.1, U1.5, U2.1, U2.2, U2.6, U2.13
VREF_THR: R25.2, R26.1, U3.6

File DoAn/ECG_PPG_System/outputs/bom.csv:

"Refs","Value","Footprint","Qty","DNP"
"C1","10uF","Capacitor_SMD:C_0805_2012Metric","1",""
"C2","100nF","Capacitor_SMD:C_0603_1608Metric","1",""
"C3","10uF","Capacitor_SMD:C_0805_2012Metric","1",""
"C4","100nF","Capacitor_SMD:C_0603_1608Metric","1",""
"C5","100pF","Capacitor_SMD:C_0603_1608Metric","1",""
"C6","47pF","Capacitor_SMD:C_0603_1608Metric","1",""
"C7","47pF","Capacitor_SMD:C_0603_1608Metric","1",""
"C8","100nF","Capacitor_SMD:C_0603_1608Metric","1",""
"C9","1nF","Capacitor_SMD:C_0603_1608Metric","1",""
"C10","1uF","Capacitor_SMD:C_0603_1608Metric","1",""
"C11","100nF","Capacitor_SMD:C_0603_1608Metric","1",""
"C12","47nF","Capacitor_SMD:C_0603_1608Metric","1",""
"C13","100nF","Capacitor_SMD:C_0603_1608Metric","1",""
"C14","22pF","Capacitor_SMD:C_0603_1608Metric","1",""
"C15","1uF","Capacitor_SMD:C_0603_1608Metric","1",""
"C16","1uF","Capacitor_SMD:C_0603_1608Metric","1",""
"C17","470nF","Capacitor_SMD:C_0603_1608Metric","1",""
"C18","100nF","Capacitor_SMD:C_0603_1608Metric","1",""
"D1","Green_PWR","LED_SMD:LED_0805_2012Metric","1",""
"D2","Red_PULSE","LED_SMD:LED_0805_2012Metric","1",""
"J1","Power_In","Connector_PinHeader_2.54mm:PinHeader_1x02_P2.54mm_Vertical","1",""
"J2","ECG_Leads","Connector_PinHeader_2.54mm:PinHeader_1x03_P2.54mm_Vertical","1",""
"J3","PPG_Sensor","Connector_PinHeader_2.54mm:PinHeader_1x04_P2.54mm_Vertical","1",""
"J4","System_Out","Connector_PinHeader_2.54mm:PinHeader_1x06_P2.54mm_Vertical","1",""
"R1","100k","Resistor_SMD:R_0603_1608Metric","1",""
"R2","100k","Resistor_SMD:R_0603_1608Metric","1",""
"R3","1k","Resistor_SMD:R_0603_1608Metric","1",""
"R4","1k","Resistor_SMD:R_0603_1608Metric","1",""
"R5","1k","Resistor_SMD:R_0603_1608Metric","1",""
"R6","10M","Resistor_SMD:R_0603_1608Metric","1",""
"R7","10M","Resistor_SMD:R_0603_1608Metric","1",""
"R8","1k","Resistor_SMD:R_0603_1608Metric","1",""
"R9","100k","Resistor_SMD:R_0603_1608Metric","1",""
"R10","100k","Resistor_SMD:R_0603_1608Metric","1",""
"R11","1M","Resistor_SMD:R_0603_1608Metric","1",""
"R12","390k","Resistor_SMD:R_0603_1608Metric","1",""
"R13","330k","Resistor_SMD:R_0603_1608Metric","1",""
"R14","39k","Resistor_SMD:R_0603_1608Metric","1",""
"R15","39k","Resistor_SMD:R_0603_1608Metric","1",""
"R16","10k","Resistor_SMD:R_0603_1608Metric","1",""
"R17","91k","Resistor_SMD:R_0603_1608Metric","1",""
"R18","1M","Resistor_SMD:R_0603_1608Metric","1",""
"R19","220R","Resistor_SMD:R_0603_1608Metric","1",""
"R20","330k","Resistor_SMD:R_0603_1608Metric","1",""
"R21","15k","Resistor_SMD:R_0603_1608Metric","1",""
"R22","15k","Resistor_SMD:R_0603_1608Metric","1",""
"R23","1k","Resistor_SMD:R_0603_1608Metric","1",""
"R24","47k","Resistor_SMD:R_0603_1608Metric","1",""
"R25","100k","Resistor_SMD:R_0603_1608Metric","1",""
"R26","10k","Resistor_SMD:R_0603_1608Metric","1",""
"R27","1k","Resistor_SMD:R_0603_1608Metric","1",""
"U1","AD623ARZ","Package_SO:SOIC-8_3.9x4.9mm_P1.27mm","1",""
"U2","MCP6004-E/SL","Package_SO:SOIC-14_3.9x8.7mm_P1.27mm","1",""
"U3","MCP6002-E/SN","Package_SO:SOIC-8_3.9x4.9mm_P1.27mm","1",""
